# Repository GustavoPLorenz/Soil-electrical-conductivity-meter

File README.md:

# Soil electrical conductivity meter

The soil electrical conductivity meter is a device designed to see how easily soil conducts electricity. It was made using an Arduino Uno R3 and transmits the data via Bluetooth to a connected cell phone. To use it, simply press the button on the board with the cell phone connected and the nails in the soil, which will then send the data to the cell phone.

# Bill of Materials
## Bill of Materials (BOM)

| Quantity | Component |
|:--------:|-----------|
| 1x | Arduino UNO R3 |
| 1x | PCB |
| 1x | Case |
| 1x | DHT11 Temperature and Humidity Sensor |
| 1x | HC-05 Bluetooth Module |
| 1x | Buzzer |
| 1x | Push Button |
| 1x | LED |
| 2x | 1kΩ Resistor |
| 1x | 10kΩ Resistor |
| 1x | 220kΩ Resistor |
| 2x | Wires |
| 2x | 10cm Iron Nail |
| 4x | M3 × 20mm Phillips Head Screw |
| 4x | M3 × 10mm Phillips Head Screw |
| 1x | 1×6 Pin Header |
| 2x | 1×8 Pin Header |
| 1x | 1×10 Pin Header |
| 1x | USB-B Connector |

# Files

<ul>
 
 <li>CAD: https://github.com/GustavoPLorenz/Soil-electrical-conductivity-meter/blob/main/CAD</li>

 <li>PCB: https://github.com/GustavoPLorenz/Soil-electrical-conductivity-meter/blob/main/Kicad</li>

 <li>Firmware: https://github.com/GustavoPLorenz/Soil-electrical-conductivity-meter/blob/main/Firmware</li>
</ul>

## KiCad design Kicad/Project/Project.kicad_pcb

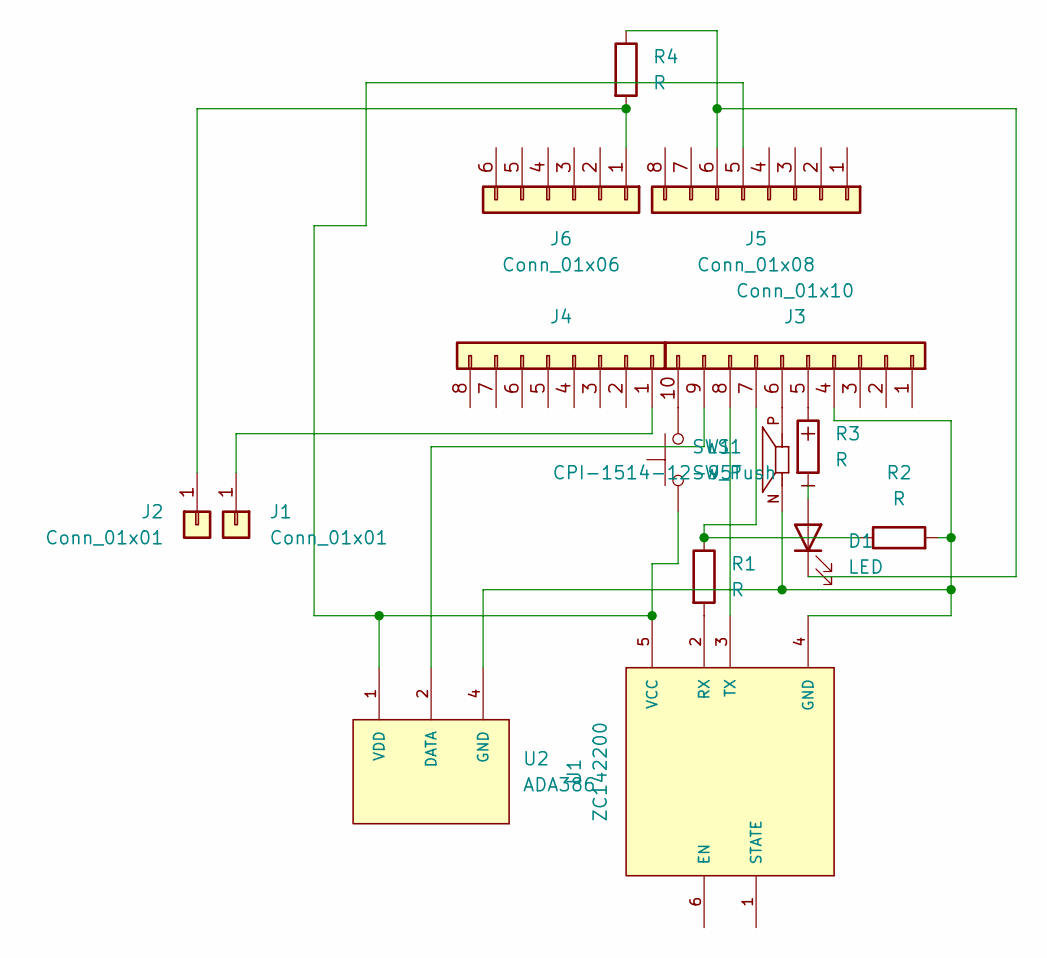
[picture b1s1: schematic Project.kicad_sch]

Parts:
D1: LED; LED_D5.0mm
J1, J2: Conn_01x01; TestPoint_Plated_Hole_D2.0mm
J3: Conn_01x10; PinHeader_1x10_P2.54mm_Vertical
J4, J5: Conn_01x08; PinHeader_1x08_P2.54mm_Vertical
J6: Conn_01x06; PinHeader_1x06_P2.54mm_Vertical
LS1: CPI-1514-12-95T; XDCR_CPI-1514-12-95T; MPN CPI-1514-12-95T
R1, R2, R3, R4: R; R_Axial_DIN0207_L6.3mm_D2.5mm_P10.16mm_Horizontal
SW1: SW_Push; SW_PUSH_6mm
U1: ZC142200; MODULE_ZC142200; MPN ZC142200
U2: ADA386; XDCR_ADA386; MPN ADA386

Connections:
unnamed: D1.2 (A), R3.2
unnamed: D1.1 (K), J5.6, R4.1
unnamed: J1.1 (Pin_1_1), J4.1 (Pin_1_1)
unnamed: J2.1 (Pin_1_1), J6.1 (Pin_1_1), R4.2
unnamed: J3.4, LS1.N, R2.2, U1.4 (GND), U2.4 (GND)
unnamed: J3.5, R3.1
unnamed: J3.6, LS1.P
unnamed: J3.7, R1.1, R2.1
unnamed: J3.8, U1.3 (TX)
unnamed: J3.9, U2.2 (DATA)
unnamed: J3.10, SW1.2
unnamed: J5.5, SW1.1, U1.5 (VCC), U2.1 (VDD)
unnamed: R1.2, U1.2 (RX)

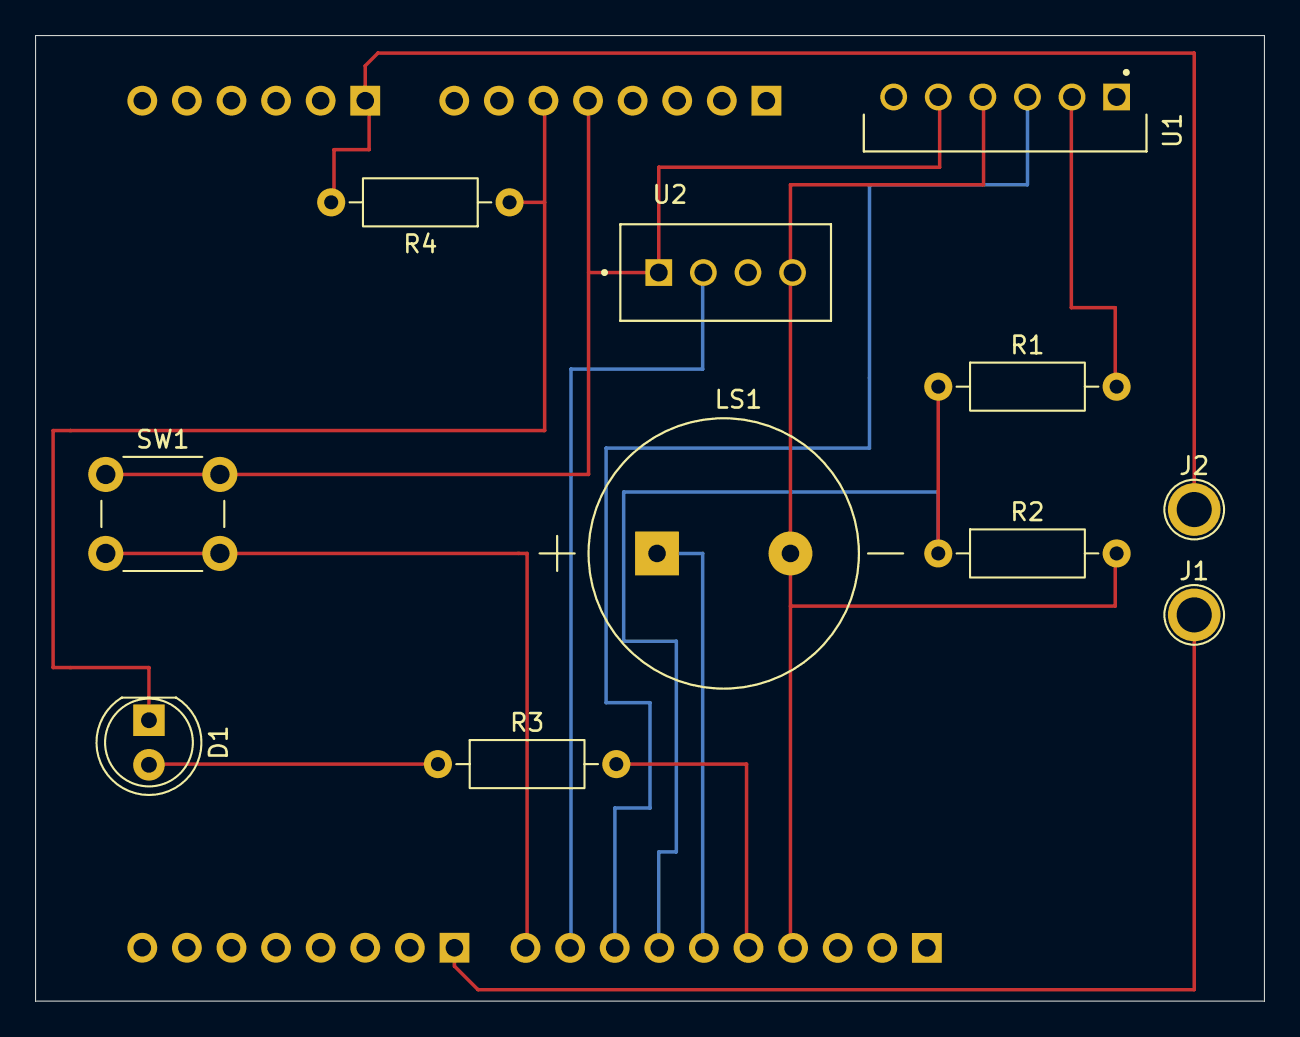
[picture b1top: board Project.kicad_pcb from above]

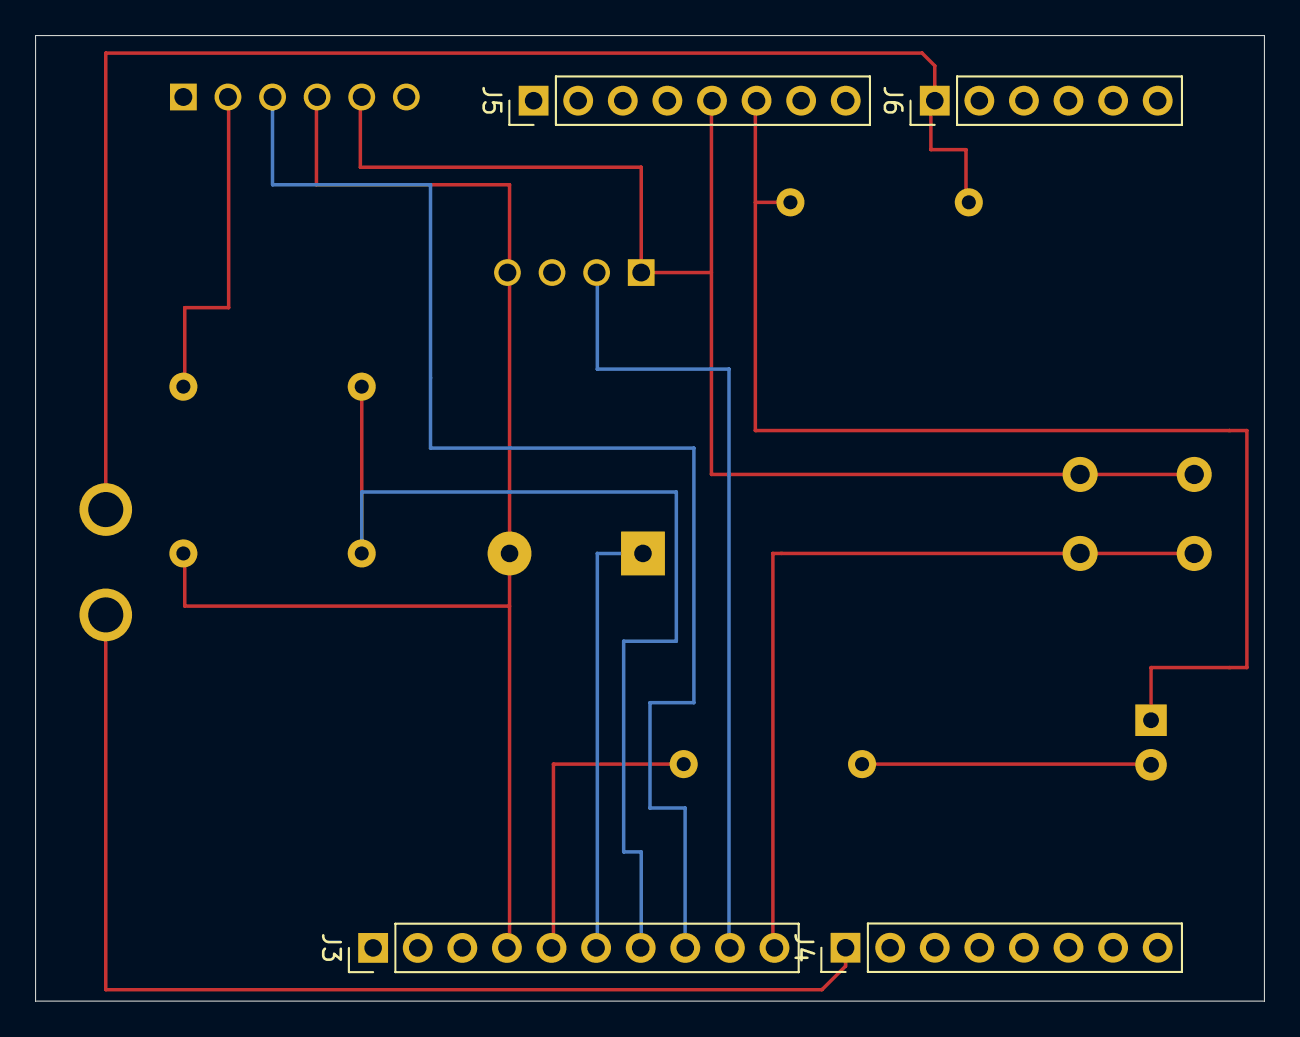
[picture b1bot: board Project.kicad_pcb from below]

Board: 2 copper layers, 70.0 x 55.0 mm, 15 parts (4 on the bottom side), 13 nets.
